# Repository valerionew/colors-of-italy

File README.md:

# Colors of Italy

# <a href="https://valerionew.github.io/colors-of-italy/" target="_blank">https://valerionew.github.io/colors-of-italy/</a>

inspired by http://www.lucadentella.it/en/2021/01/09/impariamo-insieme-mappa-dinamica-con-arduino/

Using https://github.com/wokwi/kicad-jlcpcb-bom-plugin for BOM management

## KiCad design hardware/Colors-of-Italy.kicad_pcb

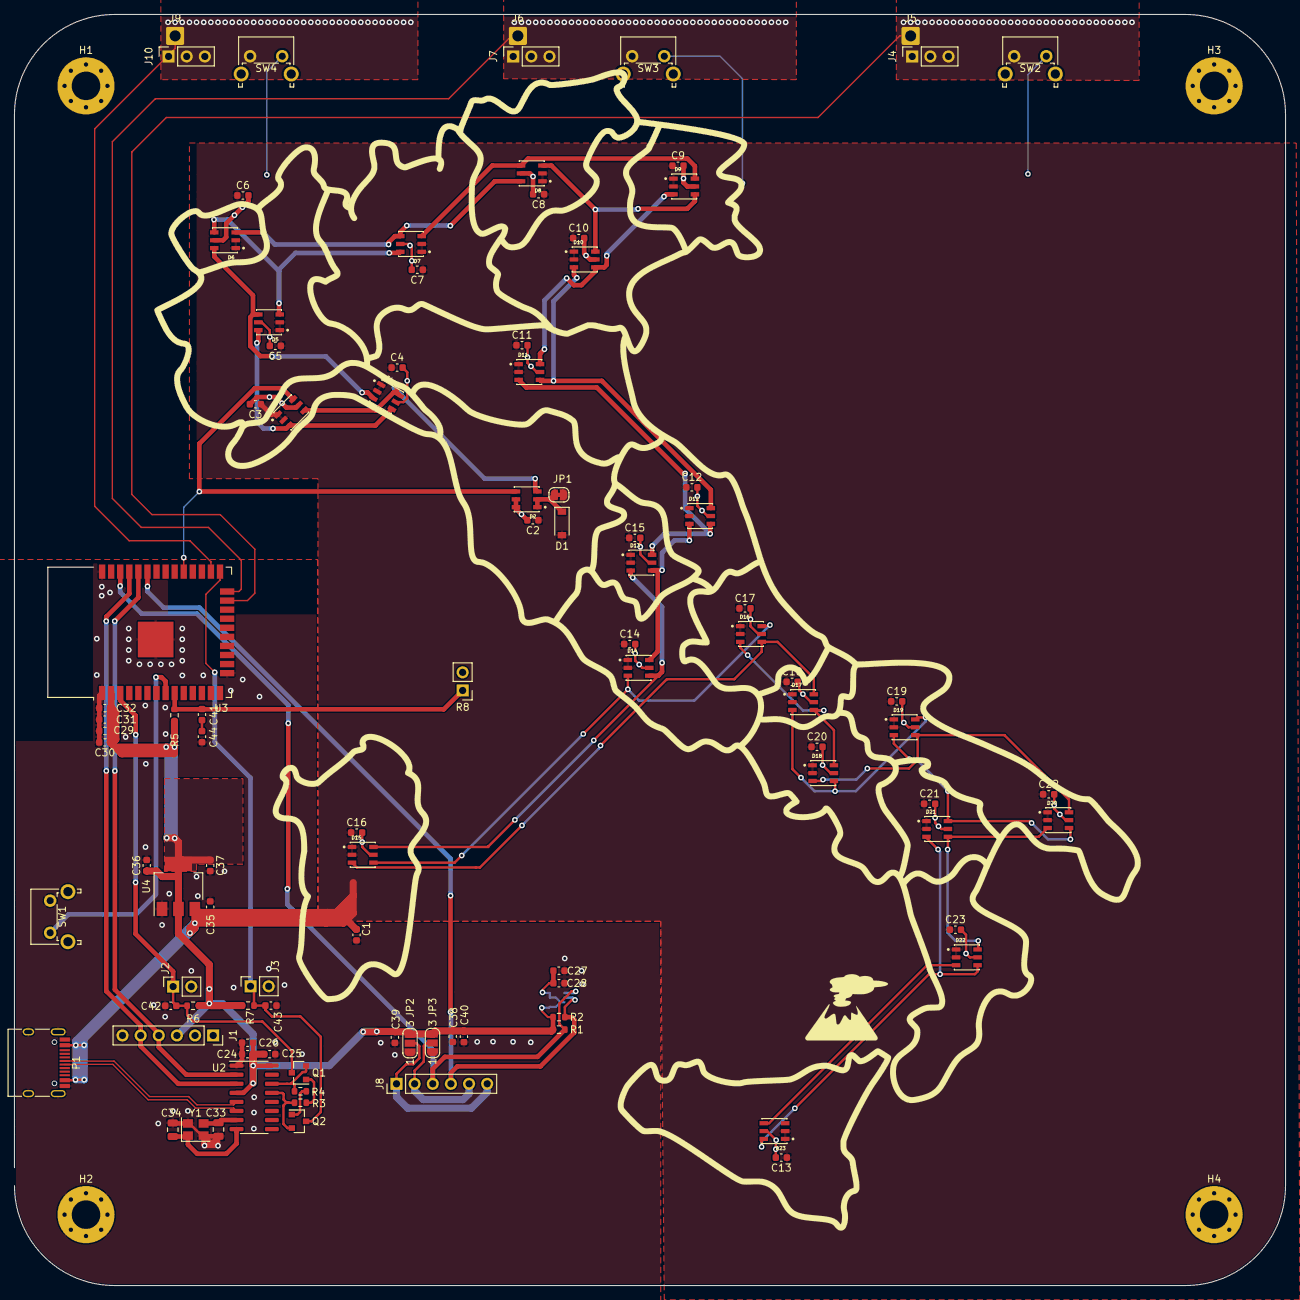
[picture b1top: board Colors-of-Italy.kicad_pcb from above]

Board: 2 copper layers, 178.0 x 178.0 mm, 104 parts (1 on the bottom side), 48 nets.

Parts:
C1, C24, C27, C29, C30, C35, C37, C38, C39, C41, C43, C44: 10u; C_0603_1608Metric
C2, C3, C4, C5, C6, C7, C8, C9, C10, C11, C12, C13, C14, C15, C16, C17, C18, C19, C20, C21, C22, C23, C25, C26, C28, C31, C32, C36, C40, C42: 100n; C_0603_1608Metric
C33, C34: 18p; C_0805_2012Metric
D1: 1N4148W; D_SOD-123
D2, D3, D4, D5, D6, D7, D8, D9, D10, D11, D12, D13, D14, D15, D16, D17, D18, D19, D20, D21, D22, D23: WS2813; LED_WS2813-MINI
H1, H2, H3, H4: MountingHole_Pad; MountingHole_4mm_Pad_Via
J1: Conn_01x06_Male; PinSocket_1x06_P2.54mm_Vertical
J2, J3: JMP; PinSocket_1x02_P2.54mm_Vertical
J4, J7, J10: Conn_01x03_Female; PinSocket_1x03_P2.54mm_Vertical
J5: Touch_Pad_+; SolderWire-0.75sqmm_1x01_D1.25mm_OD2.3mm
J6: Touch_Pad_0; SolderWire-0.75sqmm_1x01_D1.25mm_OD2.3mm
J8: Conn_01x06_Female; PinHeader_1x06_P2.54mm_Vertical
J9: Touch_Pad_-; SolderWire-0.75sqmm_1x01_D1.25mm_OD2.3mm
JP1: Jumper; SolderJumper-2_P1.3mm_Bridged_RoundedPad1.0x1.5mm
JP2, JP3: SolderJumper_3_Open; SolderJumper-3_P1.3mm_Open_RoundedPad1.0x1.5mm_NumberLabels
P1: USB_C_Plug; USB_C_Receptacle_HRO_TYPE-C-31-M-12
Q1, Q2: 2N7002; SOT-23
R1, R2, R3, R4, R5, R6, R7: 10k; R_0603_1608Metric
R8: LDR; PinHeader_1x02_P2.54mm_Vertical
SW1: SW_Push; SW_Tactile_SPST_Angled_PTS645Vx58-2LFS
SW2: SW_+_Fb; SW_Tactile_SPST_Angled_PTS645Vx58-2LFS
SW3: SW_0_Fb; SW_Tactile_SPST_Angled_PTS645Vx58-2LFS
SW4: SW_-_Fb; SW_Tactile_SPST_Angled_PTS645Vx58-2LFS
U1: BME280; Bosch_LGA-8_2.5x2.5mm_P0.65mm_ClockwisePinNumbering
U2: CH340G; SOIC-16_3.9x9.9mm_P1.27mm
U3: ESP32-WROOM-32
U4: AZ1117-3.3; SOT-223-3_TabPin2
Y1: 12MHz; Crystal_SMD_3225-4Pin_3.2x2.5mm

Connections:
+3V3: C24.1, C25.1, C26.1, C27.1, C28.1, C29.1, C30.1, C31.1, C32.1, C36.1, C37.1, C38.1, C39.1, C40.1, J1.3, JP2.3, JP3.3, R1.2, R2.2, R5.1, R6.1, R7.1, U1.2, U1.5, U1.6, U1.8, U2.4, U2.16, U3.2, U4.2
+5V: C1.1, C2.1, C3.1, C4.1, C5.1, C6.1, C7.1, C8.1, C9.1, C10.1, C11.1, C12.1, C13.1, C14.1, C15.1, C16.1, C17.1, C18.1, C19.1, C20.1, C21.1, C22.1, C23.1, C35.1, D1.2, D3.1, D3.2, D4.1, D4.2, D5.1, D5.2, D6.1, D6.2, D7.1, D7.2, D8.1, D8.2, D9.1, D9.2, D10.1, D10.2, D11.1, D11.2, D12.1, D12.2, D13.1, D13.2, D14.1, D14.2, D15.1, D15.2, D16.1, D16.2, D17.1, D17.2, D18.1, D18.2, D19.1, D19.2, D20.1, D20.2, D21.1, D21.2, D22.1, D22.2, D23.1, D23.2, JP1.1, P1.A4, P1.A9, P1.B4, P1.B9, U4.3
BOOT0: C43.1, J3.1, Q2.3, R7.2, U3.25
D+: P1.A6, U2.5
D-: P1.A7, U2.6
EN: C42.1, J2.1, Q1.3, R6.2, U3.3
GND: C1.2, C2.2, C3.2, C4.2, C5.2, C6.2, C7.2, C8.2, C9.2, C10.2, C11.2, C12.2, C13.2, C14.2, C15.2, C16.2, C17.2, C18.2, C19.2, C20.2, C21.2, C22.2, C23.2, C24.2, C25.2, C26.2, C27.2, C28.2, C29.2, C30.2, C31.2, C32.2, C33.1, C34.1, C35.2, C36.2, C37.2, C38.2, C39.2, C40.2, C42.2, C43.2, C44.2, D2.5, D2.6, D3.5, D4.5, D5.5, D6.5, D7.5, D8.5, D9.5, D10.5, D11.5, D12.5, D13.5, D14.5, D15.5, D16.5, D17.5, D18.5, D19.5, D20.5, D21.5, D22.5, D23.5, H2.1, H4.1, J1.6, J2.2, J3.2, JP2.1, JP3.1, P1.A1, P1.A12, P1.B1, P1.B12, P1.S1, R8.2, SW1.2, SW2.2, SW3.2, SW4.2, U1.1, U1.7, U2.1, U3.1, U3.15, U3.38, U3.39, U4.1, Y1.2, Y1.4
LDR: C41.1, R5.2, R8.1, U3.9
LED_CHAIN: D2.4, D3.6, U3.29
unnamed: C33.2, U2.7, Y1.3
unnamed: C34.2, U2.8, Y1.1
unnamed: C41.2, C44.1
unnamed: D1.1, D2.1, D2.2, JP1.2
unnamed: D2.3, D3.4, D4.6
unnamed: D3.3, D4.4, D5.6
unnamed: D4.3, D5.4, D6.6
unnamed: D5.3, D6.4, D7.6
unnamed: D6.3, D7.4, D8.6
unnamed: D7.3, D8.4, D9.6
unnamed: D10.3, D11.4, D12.6
unnamed: D9.3, D10.4, D11.6
unnamed: D8.3, D9.4, D10.6
unnamed: D11.3, D12.4, D13.6
unnamed: D12.3, D13.4, D14.6
unnamed: D13.3, D14.4, D15.6
unnamed: D14.3, D15.4, D16.6
unnamed: D15.3, D16.4, D17.6
unnamed: D16.3, D17.4, D18.6
unnamed: D17.3, D18.4, D19.6
unnamed: D18.3, D19.4, D20.6
unnamed: D19.3, D20.4, D21.6
unnamed: D20.3, D21.4, D22.6
unnamed: D21.3, D22.4, D23.6
unnamed: D22.3, D23.4
unnamed: J8.1, J8.6, JP2.2
unnamed: J8.2, J8.5, JP3.2
unnamed: Q1.1, R3.2
unnamed: Q1.2, R4.1, U2.14
unnamed: Q2.1, R4.2
unnamed: Q2.2, R3.1, U2.13
RX: J1.4, U2.2, U3.34
SCL: J8.3, R1.1, U1.4, U3.36
SDA: J8.4, R2.1, U1.3, U3.33
TOUCH_0: J6.1, J7.1, J7.2, J7.3, SW3.1, U3.24
TOUCH_+: J4.1, J4.2, J4.3, J5.1, SW2.1, U3.23
TOUCH_-: J9.1, J10.1, J10.2, J10.3, SW4.1, U3.26
TX: J1.5, U2.3, U3.35
WIFI_RESET: SW1.1, U3.8

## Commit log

2021-01-17 added grapics and proof of concept
2021-01-17 added mockup,regions footprint reference, created board outline
2021-01-17 added file footprint
2021-01-17 semplificato outline regioni
2021-01-17 added rounded edges to pcb
2021-01-17 moved into folders
2021-01-17 added wifi login loop
2021-01-18 wifi credentials reset if button is pressed for long enough time
2021-01-18 Fixed broken file
2021-01-18 progressi col frame
2021-01-19 Aggiunta pcb e coperchio posteriore
2021-01-20 fixed missing parenthesis triggering a compiling error
2021-01-20 added comment on library version
2021-01-20 fixed wifi credentials reset
2021-02-01 Fixed all things mechanical
2021-02-01 modified led structure to ws****b
2021-02-01 updated mechanical
2021-02-02 v1.0 schematic
2021-02-02 added useful datasheets
2021-02-02 rimossi fogli gerarchici delle regioni
2021-02-02 risolti problemi di librerie
2021-02-02 nuovi asset per bordo scheda e art interna
2021-02-02 non so cosa sia cambiato ma qualcosa è cambiato, ma ovviamente git diff non serve a nulla con i file binari quindi committo così com'è, ciaone
2021-02-02 added json parsing
2021-02-02 fixed variable types
2021-02-03 minor changes to pcb: added led footprint for comparison
2021-02-03 Added gitattributes for linguist
2021-02-03 updated libraries reference
2021-02-03 added light adaptiveness
2021-02-03 missing space-rino means a new commit-erino
2021-02-03 map now supports multiple leds for each region
2021-02-03 added region names as comments
2021-02-03 add footprint
2021-02-03 add all footprints
2021-02-03 add LCSC ref
2021-02-03 Added ch340g in the schematic
2021-02-03 aggiunto sistema di caricamento del codice
2021-02-04 add graphics,edges,keepout
2021-02-04 aggiunto show() per mostrare i led, ora controlla la luminosità ambientale ogni loop, cambiato qualche pin, cambiati i colori che erano troppo desaturati
2021-02-04 added back forgotten led 16
2021-02-04 cazzo commento a fare che tanto faremo il rebase
2021-02-04 aggiunto sito dummy per testing, modificato arancione, modificata lum minima
2021-02-04 fixed led somehow
2021-02-04 updated schematic
2021-02-04 removed battery
2021-02-09 hardware cleanup, bump to next mechanical
2021-02-09 New mechanical version: lite
2021-02-09 unified pins
2021-02-09 aggiunti pulsanti fallback se non funzionasse il touch
2021-02-10 first layout draft
2021-02-10 Aggiunti bottoni touch, rotti board edges
2021-02-10 did some initial routing
2021-02-11 first routing try
2021-02-12 routing optimization
2021-02-12 move oled, change tracks
2021-02-12 optimize routing under ESP, gnd plane, OLED position
2021-02-12 Fixed oled connector, fixed programming connector, added mounting points
2021-02-12 layout properly sminchied for the happiness of giacomo
2021-02-13 pin swapping for layout
2021-02-13 second fucking routing for the joy of balerio
2021-02-13 dio stracane se sto sbroglio non va bene Maria io esco
2021-02-13 fix touchplates, optim traces and gnd fills
2021-02-14 Consolidated BOM
2021-02-14 added heatsink for regulator
2021-02-16 last routing
2021-02-16 Modified fields for JLCPCB BOM Assembly plugin
2021-02-16 improved zone rules
2021-02-16 optimise touch plate traces and keepout
2021-02-17 flipped bme280 to get measurement from a window on the back
2021-02-18 added graphics, merged diverging branch
2021-02-19 back graphics
2021-02-23 optimise back graphics
2021-02-25 exported cpl bom and fixed graphics
2021-02-27 change new ws footprints
2021-02-27 changing to ws2811 for manufacturability
2021-02-27 realligned usb in frame
2021-02-27 added missing led ground
2021-02-28 increased spacing between touch pads as per st appnote
2021-02-28 route ws2813 mini and export
2021-02-28 fix last commit, add untracked files
2021-03-01 Added production files
2021-03-11 aggiunte regioni corrette come da hardware
2021-03-13 added reset handling during connection, color fetching from internet
2021-03-13 aggiornato divisorio regioni per avere linee più spesse
2021-03-13 fixed wifi reset, added wifi animation
2021-03-13 added comment in callback function
2021-03-13 fixed timing
2021-03-13 added light mapping
2021-03-14 added platformio integration
2021-03-14 Revert "added platformio integration"
    This reverts commit 3a084464e693f5521962d383da1e6be5d9bf1720.
2021-03-14 Revert "Revert "added platformio integration""
    This reverts commit 2585713621e31f486d2586a19b9453a0f3b17e27.
2021-03-14 removed old files
2021-03-14 Moved debug def in debug environment and using COM* ports bc non so installare gentoo
2021-03-16 main.cpp split in multiple files
2021-03-16 fixed merge conflicts
2021-03-17 changed network default name
2021-03-17 change file names to colors of italy
2021-03-17 change file names to colors-of-italy
2021-03-18 created color testing tool
2021-03-18 added color correction, increased colors buffer size
2021-03-18 color defaults to red
2021-03-18 ye olde copy-and-paste manual branch
2021-03-18 ye olde manual branch merging failed, gotta do some more manual merging to fix ye olde failed manual merging
2021-03-18 Modified frame to use M4 nuts, bigger frame size to round up in cura
2021-03-18 modified assets for regions dividers
2021-03-18 Added exports from kicad in assets
2021-03-18 added manufacturability sources
2021-03-18 improved regioni
2021-03-21 moved folders, created new sketch
2021-03-21 brightness calibration done
2021-03-21 added brightness fix for blue
2021-03-22 fixed blue, added brightness control
2021-03-22 updated light control
2021-03-22 fine tuning of map rescale values
2021-03-22 fixed
2021-03-22 removed overdefinition of debug constant
2021-03-23 led calibration no more
2021-03-23 fixed algorithm
2021-03-23 added comments
2021-03-23 fixed comment
2021-03-23 added LED color correction
2021-03-23 refactored constants
2021-03-23 more refactoring
2021-03-23 code refactoring (again)
2021-03-23 updated button class
2021-03-23 𝒶𝓋𝒶𝓃𝓏𝒶𝓂ℯ𝓃𝓉𝒾 𝓈𝒾ℊ𝓃𝒾𝒻𝒾𝒸𝒶𝓉𝒾𝓋𝒾 𝓃ℯ𝓁𝓁𝒶 ℊℯ𝓈𝓉𝒾ℴ𝓃ℯ 𝒹ℯ𝒾 𝓅𝓊𝓁𝓈𝒶𝓃𝓉𝒾
2021-03-23 ｍｏｒｅ ｉｍｐｒｏｖｅｍｅｎｔｓ ａｎｄ ｓｔｕｆｆ
2021-03-23 dicevano che era impossibile, ma ce l'abbiamo fatta
2021-03-24 improved gitignore
2021-03-24 added possibility to change partition table to minimize spfss
2021-03-24 Improved touch buttons user interface: smaller and off-center
2021-03-24 seems good, doesn't work
2021-03-24 another test
2021-03-24 Brand new ota code brand new lorenzo
2021-03-24 it's like before, excepts that it works now 🍆🍑💦💦💦
2021-03-24 ADDED VERSION CONTROL
2021-03-24 small fix to version control
2021-03-24 code refactoring, successfully re-invented wheel (BUT DOES IT LOOK PRETTY?)
2021-03-24 Ooops bug fixerino
2021-03-25 added buffer
2021-03-26 debug output
2021-03-26 better button handling (filter fixed, added circular buffer)
2021-03-26 added wifi timeout
2021-03-26 debug print in touch test example
2021-03-26 added fillet to frame buttons
2021-03-26 ＨＵＧＥ ＢＵＧＦＩＸＥＳ and stuff
2021-03-26 fixed board outline
2021-03-26 migliorato modello 3D, ora contiene front e back
2021-03-26 fixed url
2021-03-26 fixes and stuff (now actually works)
2021-03-26 first semi-working version (needs testing, i'm not sure it actually works BECAUSE WTF IS CORS)
2021-03-26 forgot to change url
2021-03-26 spacing
2021-03-26 added spinner
2021-03-26 change docs folder capitalization for gh pages
2021-03-26 enabled error logging in console
2021-03-26 switched to https
2021-03-26 styling fixes
2021-03-26 fixed styling
2021-03-26 updated to valerio stop piansing (technical term)
2021-03-26 more fixes, less balerio pianserinos
2021-03-26 modify html doc
2021-03-26 added text, fixed styling
2021-03-26 added favicon
2021-03-26 added animations
2021-03-26 added some text
2021-03-26 style fixes
2021-03-26 correzioni nel testo della pagina
2021-03-26 aggiunto chi siete, da completare
2021-03-26 change web page name
2021-03-26 Modifiche minori a css e html
2021-03-26 cambiato testo del chi siamo
2021-03-26 added images
2021-03-26 improved website, inserted images, corrected text
2021-03-26 cleaned code, added credits
2021-03-26 added thumbnail image for socials
2021-03-26 Corretto testo del sito
2021-03-26 fixed thumbnail
2021-03-26 added social meta tags
2021-03-26 migliorata pagina web
2021-03-26 added bold for some words
2021-03-26 sistemato campo email, rimosso css senza senso
2021-03-26 updated ebay link
2021-03-26 rimossa frase dubbia dalla pagina HTML
2021-03-27 added pictures
2021-03-27 fixes nella pagina web
2021-03-27 fixed back dxf file
2021-03-27 clean up
2021-03-28 added anglish language
2021-03-28 removed duplicate link
2021-03-28 added language flags
2021-03-28 now esp gets reset when wifi connections fails for a long time
2021-03-28 small refactoring
2021-03-30 fixed img location
2021-03-31 Propagated changes of the frame to 3MF and STL files
2021-04-10 added debug prints before resets
2021-04-10 it's nice that we did all the work to blend at low light but we should actually use our work instead of throwing it away lmao
2021-04-10 Revert "change file names to colors-of-italy"
    This reverts commit ad0706144210016f2d85405e123c87676c1ebd15.
2021-04-10 renamed correcly files after last revert
2021-04-10 added schematic pdf
2021-04-12 fixed merge bugs
2021-04-20 added prints for debug
2021-04-20 changed touch button threshold to 70
2021-04-20 moved tools in a separate folder
2021-04-23 added internals image, modified readme
2021-04-23 did an oopsie: not added readme.md in last commit
2022-08-08 Positives of Italy
    - First working version after the abandonment by the health ministry of the concept of the colors of the regions.
    - Removed the need for an intermediate server, now the data is taken directly from the original dB
    - Added Splashscreen with Italian flag
    - Implemented Esp reset with short click on key
    - increased upload speed during developent
    - fixed build errors due to incompatibility between old WiFiManager library and new Esp core
2022-08-08 Add files via upload
    - improved calculation of percentages for color selection
    - improved color selection
2022-08-08 improved thresholds for color selection
2022-08-08 Colors-of-Italy-pcb.png
2022-08-31 Modifiche post PR review
2022-09-01 Positives of italy (#42)
    * Positives of Italy
    - First working version after the abandonment by the health ministry of the concept of the colors of the regions.
    - Removed the need for an intermediate server, now the data is taken directly from the original dB
    - Added Splashscreen with Italian flag
    - Implemented Esp reset with short click on key
    - increased upload speed during developent
2022-09-01 changes to mechanical files
2022-09-01 specifying platform verison and port
2022-10-06 little cleanup here and there to remove dinamic allocation as much as possible
2022-10-07 Init map + splashscreen
    spostati in defines.h i colori e inizializzata a NERO la MAP
2022-10-07 made capoacitative butto work, hopefully
2022-10-08 cleaning up a little bit, reset disabled as goes crazy
2022-10-08 added missing files
2022-10-12 Risistemata sensore luce ambientale
